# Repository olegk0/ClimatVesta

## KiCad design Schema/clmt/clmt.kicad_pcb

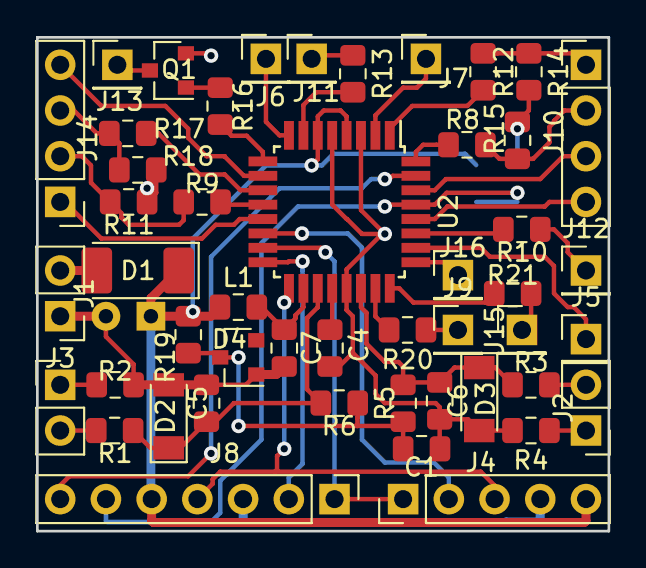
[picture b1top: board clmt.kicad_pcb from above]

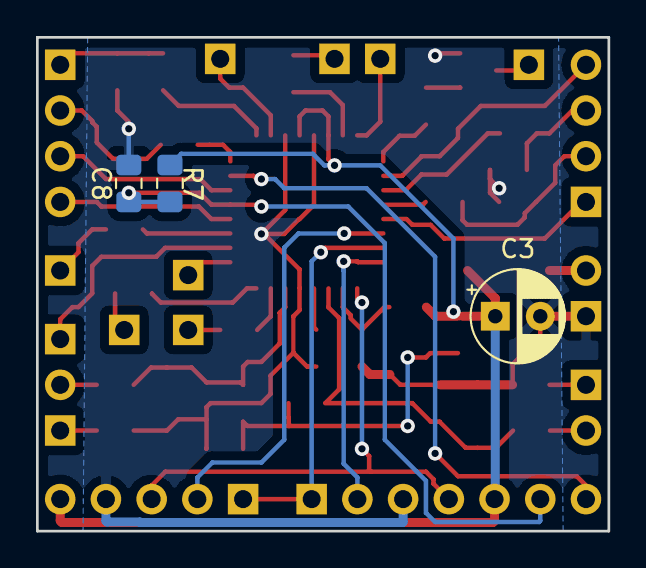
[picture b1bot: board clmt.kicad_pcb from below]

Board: 2 copper layers, 31.7 x 27.4 mm, 51 parts (3 on the bottom side), 45 nets.

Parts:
C1, C4, C5, C6, C7, C8: C; C_0805_2012Metric_Pad1.15x1.40mm_HandSolder
C3: CP1; CP_Radial_D5.0mm_P2.50mm
D1: D; D_2010_5025Metric_Castellated
D2, D3: D_Zener; D_MiniMELF
D4: BZX84Cxx; D_SOT-23_ANK
J1: Ispr T; PinHeader_1x02_P2.54mm_Vertical
J2: Salon T; PinHeader_1x02_P2.54mm_Vertical
J3: Power; PinHeader_1x02_P2.54mm_Vertical
J4: Programm; PinHeader_1x07_P2.54mm_Vertical
J5: NightLight_in; PinHeader_1x01_P2.54mm_Vertical
J6: CondEnable_out; PinHeader_1x01_P2.54mm_Vertical
J7: ACC_in; PinHeader_1x01_P2.54mm_Vertical
J8: Display; PinHeader_1x05_P2.54mm_Vertical
J9: pc0; PinHeader_1x01_P2.54mm_Vertical
J10: Encoder_T; PinHeader_1x04_P2.54mm_Vertical
J11: Hi_Mode; PinHeader_1x01_P2.54mm_Vertical
J12: Cond_Switch_in; PinHeader_1x01_P2.54mm_Vertical
J13: Cond_Ied_out; PinHeader_1x01_P2.54mm_Vertical
J14: Encoder_Vent; PinHeader_1x04_P2.54mm_Vertical
J15: pc1; PinHeader_1x01_P2.54mm_Vertical
J16: pc2; PinHeader_1x01_P2.54mm_Vertical
L1: INDUCTOR; L_0805_2012Metric_Pad1.15x1.40mm_HandSolder
Q1: BC847; SOT-23
R1, R2, R3, R4, R5, R6, R7, R8, R9, R10, R11, R12, R13, R14, R15, R16, R17, R18, R20, R21: R; R_0805_2012Metric_Pad1.15x1.40mm_HandSolder
R19: 270; R_0805_2012Metric_Pad1.15x1.40mm_HandSolder
U2: ATmega328P-AU; TQFP-32_7x7mm_P0.8mm

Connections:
/TXD: J4.7, U2.31
GND: C1.1, C3.2, C4.2, C5.2, C6.2, C7.2, C8.1, D2.2, D3.2, D4.2, J3.1, J4.3, J8.4, Q1.2, R2.2, R4.2, R11.1, R14.2, R15.1, R18.2, U2.3, U2.5, U2.21
unnamed: C1.2, D4.1, R5.1, R6.1, R19.2
unnamed: C4.1, U2.20
unnamed: C5.1, D2.1, R1.2, R6.2, U2.19
unnamed: C6.1, D3.1, R3.2, R5.2, U2.22
unnamed: C7.1, L1.2, U2.18
unnamed: C8.2, J4.6, R7.1, U2.29
unnamed: D1.2, J3.2
unnamed: J1.1, R2.1
unnamed: J1.2, R1.1
unnamed: J2.1, R4.1
unnamed: J2.2, R3.1
unnamed: J4.1, J8.1, U2.15
unnamed: J4.2, U2.16
unnamed: J4.4, J8.3, U2.17
unnamed: J5.1, U2.26
unnamed: J6.1, U2.8
unnamed: J7.1, U2.2
unnamed: J8.2, U2.14
unnamed: J9.1, R20.1
unnamed: J10.1, R12.1, R14.1
unnamed: J10.2, R8.1, R15.2
unnamed: J10.3, U2.30
unnamed: J10.4, U2.28
unnamed: J11.1, R13.1
unnamed: J12.1, R10.1
unnamed: J13.1, Q1.3
unnamed: J14.1, U2.13
unnamed: J14.2, R9.1, R11.2
unnamed: J14.3, R17.1, R18.1
unnamed: J14.4, U2.10
unnamed: J15.1, R21.1
unnamed: J16.1, U2.25
unnamed: Q1.1, R16.1
unnamed: R8.2, U2.32
unnamed: R9.2, U2.12
unnamed: R10.2, U2.27
unnamed: R12.2, U2.1
unnamed: R13.2, U2.7
unnamed: R16.2, U2.9
unnamed: R17.2, U2.11
unnamed: R20.2, U2.23
unnamed: R21.2, U2.24
VCC: C3.1, D1.1, J4.5, J8.5, L1.1, R7.2, R19.1, U2.4, U2.6

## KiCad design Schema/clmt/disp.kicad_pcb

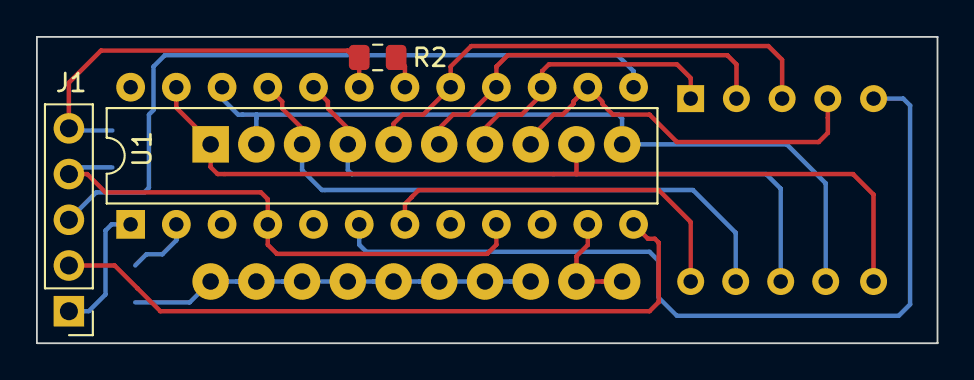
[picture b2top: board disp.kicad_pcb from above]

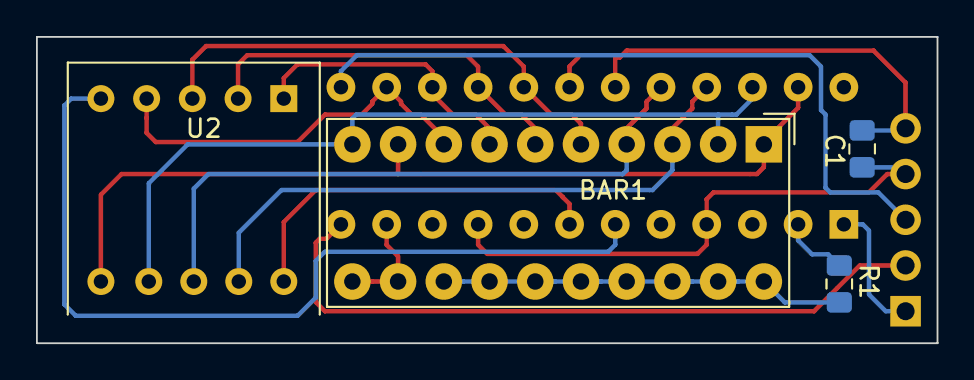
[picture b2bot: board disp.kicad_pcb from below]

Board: 2 copper layers, 50.0 x 17.0 mm, 7 parts (4 on the bottom side), 19 nets.

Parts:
BAR1: HDSP-4830_2; HDSP-4830
C1: C; C_0805_2012Metric_Pad1.15x1.40mm_HandSolder
J1: Display; PinHeader_1x05_P2.54mm_Vertical
R1, R2: R; R_0805_2012Metric_Pad1.15x1.40mm_HandSolder
U1: MAX7219; DIP-24_W7.62mm
U2: HDSM-543B; LED_036-2

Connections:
unnamed: BAR1.1, BAR1.9, U1.23, U2.6
unnamed: BAR1.3, U1.21, U2.9
unnamed: BAR1.4, U1.20, U2.8
unnamed: BAR1.5, U1.17, U2.3
unnamed: BAR1.6, U1.16, U2.2
unnamed: BAR1.7, U1.15, U2.1
unnamed: BAR1.8, U1.14, U2.4
unnamed: BAR1.2, BAR1.10, U1.22, U2.7
unnamed: BAR1.11, BAR1.12, U1.11
unnamed: BAR1.13, BAR1.14, BAR1.15, BAR1.16, BAR1.17, BAR1.18, BAR1.19, BAR1.20, R1.1
unnamed: C1.1, J1.4, U1.4, U1.9
unnamed: C1.2, J1.5, R2.1, U1.19
unnamed: J1.1, U1.1
unnamed: J1.2, U1.12
unnamed: J1.3, U1.13
unnamed: R1.2, U1.2
unnamed: R2.2, U1.18
unnamed: U1.6, U2.5
unnamed: U1.7, U2.10

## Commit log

2022-07-21 init
